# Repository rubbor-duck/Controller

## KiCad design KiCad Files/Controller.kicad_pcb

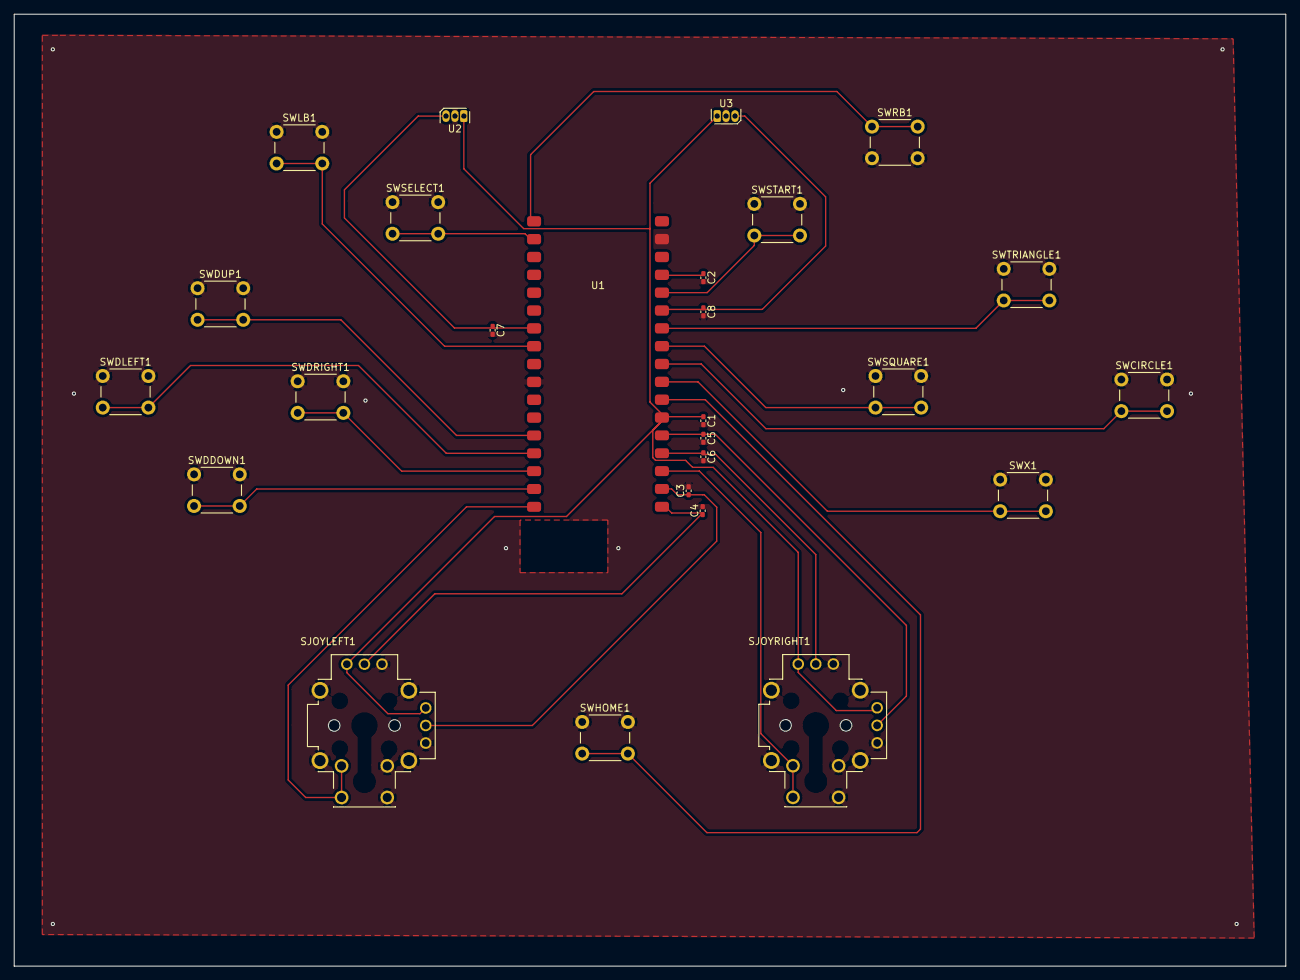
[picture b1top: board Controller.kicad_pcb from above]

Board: 2 copper layers, 181.0 x 135.5 mm, 26 parts (0 on the bottom side), 24 nets.

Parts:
C1, C2, C3, C4, C5, C6, C7, C8: 100uF; C_0402_1005Metric_Pad0.74x0.62mm_HandSolder
SJOYLEFT1: RKJXV122400R; SW_RKJXV122400R
SJOYRIGHT1: RKJXV122400R; SW_RKJXV122400R
SWCIRCLE1: SW_Push_Dual; SW_PUSH_6mm_H4.3mm
SWDDOWN1: SW_Push_Dual; SW_PUSH_6mm_H4.3mm
SWDLEFT1: SW_Push_Dual; SW_PUSH_6mm_H4.3mm
SWDRIGHT1: SW_Push_Dual; SW_PUSH_6mm_H4.3mm
SWDUP1: SW_Push_Dual; SW_PUSH_6mm_H4.3mm
SWHOME1: SW_Push_Dual; SW_PUSH_6mm_H4.3mm
SWLB1: SW_Push_Dual; SW_PUSH_6mm_H4.3mm
SWRB1: SW_Push_Dual; SW_PUSH_6mm_H4.3mm
SWSELECT1: SW_Push_Dual; SW_PUSH_6mm_H4.3mm
SWSQUARE1: SW_Push_Dual; SW_PUSH_6mm_H4.3mm
SWSTART1: SW_Push_Dual; SW_PUSH_6mm_H4.3mm
SWTRIANGLE1: SW_Push_Dual; SW_PUSH_6mm_H4.3mm
SWX1: SW_Push_Dual; SW_PUSH_6mm_H4.3mm
U1: ProS3D; ProS3_SMD
U2: LT; TO-92S
U3: RT; TO-92S

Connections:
/3V3: C2.1, U1.4 (3V3)
/3V3Switched: C1.1, SJOYLEFT1.VR1_3 (X_3.3v), SJOYLEFT1.VR2_3 (Y_3.3V), SJOYRIGHT1.VR1_3 (X_3.3v), SJOYRIGHT1.VR2_3 (Y_3.3V), U1.12 (LDO2_OUT), U2.1 (V_{CC}), U3.1 (V_{CC})
/Circle: SWCIRCLE1.2, U1.9 (IO5)
/DDOWN: SWDDOWN1.2, U1.19 (IO41)
/DLEFT: SWDLEFT1.2, U1.21 (IO39)
/DRIGHT: SWDRIGHT1.2, U1.20 (IO40)
/DUP: SWDUP1.2, U1.22 (IO38)
/Home: SWHOME1.2, U1.11 (IO0)
/JoyLeftX: C3.1, SJOYLEFT1.VR1_2 (X_REF), U1.16 (IO13)
/JoyLeftY: C4.1, SJOYLEFT1.VR2_2 (Y_REF), U1.17 (IO12)
/JoyRightX: C5.1, SJOYRIGHT1.VR1_2 (X_REF), U1.13 (IO16)
/JoyRightY: C6.1, SJOYRIGHT1.VR2_2 (Y_REF), U1.14 (IO15)
/L3: SJOYLEFT1.A, SJOYLEFT1.B, U1.18 (IO42)
/LB: SWLB1.2, U1.27 (IO6)
/LT: C7.1, U1.28 (IO7), U2.3 (V_{OUT})
/R3: SJOYRIGHT1.A, SJOYRIGHT1.B, U1.15 (IO14)
/RB: SWRB1.1, U1.34 (IO35)
/RT: C8.1, U1.6 (IO2), U3.3 (V_{OUT})
/Select: SWSELECT1.2, U1.33 (IO37)
/Square: SWSQUARE1.2, U1.8 (IO4)
/Start: SWSTART1.2, U1.5 (IO1)
/Triangle: SWTRIANGLE1.2, U1.7 (IO3)
/X: SWX1.2, U1.10 (IO21)
GND: C1.2, C2.2, C3.2, C4.2, C5.2, C6.2, C7.2, C8.2, SJOYLEFT1.C, SJOYLEFT1.D, SJOYLEFT1.SH1 (SHIELD), SJOYLEFT1.SH2 (SHIELD), SJOYLEFT1.SH3 (SHIELD), SJOYLEFT1.SH4 (SHIELD), SJOYLEFT1.VR1_1 (X_GND), SJOYLEFT1.VR2_1 (Y_GND), SJOYRIGHT1.C, SJOYRIGHT1.D, SJOYRIGHT1.SH1 (SHIELD), SJOYRIGHT1.SH2 (SHIELD), SJOYRIGHT1.SH3 (SHIELD), SJOYRIGHT1.SH4 (SHIELD), SJOYRIGHT1.VR1_1 (X_GND), SJOYRIGHT1.VR2_1 (Y_GND), SWCIRCLE1.1, SWDDOWN1.1, SWDLEFT1.1, SWDRIGHT1.1, SWDUP1.1, SWHOME1.1, SWLB1.1, SWRB1.2, SWSELECT1.1, SWSQUARE1.1, SWSTART1.1, SWTRIANGLE1.1, SWX1.1, U1.2 (GND), U1.25 (GND), U2.2 (GND), U3.2 (GND)

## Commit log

2026-05-15 Backing up Controller Project
2026-05-16 working on buttons and analog inputs
2026-05-17 Added Bounce2 library to remove bounce from switches.
    Finished the code for analog signals, buttons, and the dpad.
    Added a way to send the battery level to the computer.
    Added a 5 minute idle timer that causes the controller to go to sleep. The controller can only be woken up by the home button.
    TODO: Set the GPIO pin numbers to the correct ones.
2026-05-18 Bug fixing on breadboard
2026-05-20 Tried to fix more stuff. It just broke more ;(
2026-05-20 more issues ;(
2026-05-20 All buttons now work proprerly : )
2026-05-20 need to finish axis so I can print the pcb board
2026-05-23 unPairingTask has been HEALED!!!!
2026-05-24 Sleep now kind of works. Still keeps on waking up right after the device goes to sleep.
2026-06-04 Add files via upload
    Work In Progress Kicad files
2026-06-04 Put KiCad files into their own folder
2026-06-26 Updated to current KiCad Design
